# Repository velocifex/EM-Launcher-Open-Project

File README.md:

# Open-Source Electromagnetic Launcher (Coilgun) Development
This is a project to continually improve and implement open-source designs for coilguns, which are a type of electromagnetic (E.M.) launcher. This repository has files and information about the hardware and software for the designs under development.

# Help Wanted!
>This repo currently encapsulates a working but underperforming prototype. **It is meant as a starting point to improve upon.**
>
>It would be very helpful if individuals with electrical engineering skills could contribute to the project, especially to improve the circuit design (both schematics and layout).
>
>As stated below, **"this coilgun project aims to become the long-developed, widespread project that always could have been, but sadly never was."**

# Legality Notice
Physically producing some parts of this project may be legally prohibited in some jurisdictions. Please be aware of any laws that may apply to you before participating in this project in any way.

# Overview Explanation
Here is one very good and quick explanation of coilguns:
https://www.youtube.com/shorts/EF3v-DWCZcQ

In summary, a coilgun is fundamentally a type of electromagnetic motor, a linear switched reluctance motor to be exact. Like other electric motors it has:
- An armature to be moved. On rotating motors this is the rotor, and on a coilgun it is the projectile or launch vehicle.
	- For most coilguns including this one, the projectile is made partly or entirely of ferromagnetic material.
- Electromagnets to exert a force. On rotating motors this is the stator, while on a coilgun they are arranged along the launch track or "barrel".
	- For most coilguns including this one, these are solenoids. Usually the cross-sectional shape is circular, but this project has experimented with flat-plate rectangles as well.
	- There are usually sets of coils connected as a "phase" in rotating motors, while in coilguns there is usually one coil per "stage".
- Sensors to detect the position of the armature so the right coil(s) can be turned on or off.
- Control circuitry to switch power to specific coils on or off. This could be simply hooking up the coils' switches directly to the sensors in some ways, or using a microcontroller to have more complex switching behavior.
	- In this coilgun project, a microcontroller has been used so far, but a more simple logic circuit could be developed.

# Contents
This repo has files and instructions to do or make the following to construct the current (starting) version of the prototype:
- PCBs from online prototyping services for parts like the power switching circuits. These are in the "Hardware/Electrical" folder.
- Circuits on soldered or solderless prototyping boards for other parts that do not have or need PCBs. These are also in the "Hardware/Electrical" folder.
- 3D print the structural parts like the bobbins for the electromagnet coils. These are in the "Hardware/Mechanical" folder.
- Program microcontrollers to read sensors and switch the coils on or off. These are in the "Software" folder.
To reiterate: this prototype is just the most recent one in development, it has not yet fully achieved the project goal. The information provided in this repo is mainly to see how it was designed, so that it may be improved.

# Goals and Progress
The first milestone goal of this project is to make a coilgun which can launch something with **100m/s speed** and preferably as close to **100J kinetic energy** as possible.
Ideally it should be as energy-efficient as possible too, to make the design feasible to scale up or implement in any real-world use case.

Tests of this repo's developmental prototype as of November 14, 2026 have only achieved about 20m/s with a 44g (.044kg) projectile, giving about 8.8J of kinetic energy. This is about 9% efficient, which is above average for coilgun designs.

The project goal is proven to be feasible with existing commodity components! Several academic and hobbyist/amateur designs have already achieved such performance, but were never made open-source or otherwise did not see further development or community participation. **This coilgun project aims to become the long-developed, widespread project that always could have been, but sadly never was.**

# Possible Next Steps
- **Optimize coil geometry** i.e. wire diameter and number of turns, and consequently its electrical characteristics i.e. inductance and resistance, to create the most force! While also being decently efficient.
	- This is really the main problem to solve for a coilgun!
	- A technique for optimizing the coils has been developed, but it should be scrutinized by others. It's also very technical so it will not be repeated right here.
- Better projectile position sensors, preferably based on inductive sensing.
	- There could be a separate sensor coil in place of the existing photo-gate or contact sensors now, or sensing could be tried on the drive coils themselves.
- Change the control circuit to a simple logic-gate circuit that each stage has a copy of.
	- Would not directly improve efficiency but might make scaling up the number of stages easier.
- Capacitor energy recovery after coils shut off.
	- This would likely require high and low side switching of power to the coils which adds complexity to the power circuit design.
- Gate drive transformer for the power transistors instead of gate driver ICs.
	- This could help simplify the power switching circuit design, especially if it is going to be changed to high and low side switching.
- Set up a simulation to test lots of coil shapes more quickly than building them physically.
	- FreeCAD and ElmerFEM together would work great for this.
- Try different projectile shapes like the typical cylinder or maybe hollow ring/tube. The coils' cross-sectional shape would be different but the strategy to optimize them would be the same.
	- All existing switching and sensing components could be reused regardless of coil shape.

# Other Good Coilgun Projects
- Levi Janssen
	- Youtube channel: https://www.youtube.com/c/LeviJanssen
	- Series of videos about coilgun design:
		- https://www.youtube.com/watch?v=Xh28YdN8uP0&list=PLKl_Ihtuj1fpWz5WA09WJIgf677wJ2ihX (playlist)
		- https://www.youtube.com/watch?v=n-MfA9tIX5s and https://www.youtube.com/watch?v=OzI8P56p3pk (these last two videos in the series aren't in the above playlist)
- Electronoobs
	- Youtube channel: https://www.youtube.com/@ELECTRONOOBS/featured
	- Some videos on his coilgun projects:
		- https://www.youtube.com/watch?v=bGfrwBl-Q-A
		- https://www.youtube.com/watch?v=vtoWxGVx5kA
- OwenAir8242
	- Youtube channel: https://www.youtube.com/@owenair8242
	- This channel has some very good performing coilguns that achieve the 100m/s goal:
		- https://www.youtube.com/watch?v=5a4ZcsGYLRs
		- https://www.youtube.com/shorts/ZIMWo178rbU
		- https://www.youtube.com/shorts/G4_D2fhIGVg
- Tokamake
	- Youtube channel: https://www.youtube.com/@Tokamake
	- There are some excellently performing coilguns on this channel, including ones that much exceed the 100m/s speed goal! For example:
		- https://www.youtube.com/shorts/MI6NMF4MVIE
		- https://www.youtube.com/shorts/5vRxPeuDqeQ
		- https://www.youtube.com/shorts/phLoA5XnM9Y
- Owen Welsh
	- Youtube channel: https://www.youtube.com/@owensprojects
	- Some videos on his coilgun projects:
		- https://www.youtube.com/watch?v=BBhZLNdyRro
		- https://www.youtube.com/watch?v=rotrRg4ZUpk
		- https://www.youtube.com/watch?v=9OQUBITIkow

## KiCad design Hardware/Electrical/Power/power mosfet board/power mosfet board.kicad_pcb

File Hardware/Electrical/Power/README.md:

This is the circuit which turns power to one coil on or off. Below are some pictures and descriptions of the parts on the PCB.
The most important part is the high-power MOSFET which is a type of transistor switch. This particular design uses Goford brand MOSFET, product code GT020N10TL, which is rated to 100V drain-to-source and 300A continuous current, although it can briefly handle higher currents if done infrequently.
The next most important part is the MOSFET gate driver IC which helps quickly and safely make the MOSFET conductive or not, corresponding to the coil being powered "on" or "off" respectively. It also provides galvanic isolation between the low-voltage control circuitry and higher-voltage main power rails for safety. Accordingly, it has its own +15V isolated power supply located on another board (not shown below) and plugged into one of the connectors. Each board has two power supply input connectors so they can be daisy-chained together and use less wire.
Another important part is the flyback diode (also called crowbar diode) which lets the coil current continue flowing briefly after it is shut off (disconnected from main power) and dissipate its energy through its own wire resistance. Without this component, there would be a huge inductive voltage spike across the MOSFET when it tries to stop conducting, which could easily cause breakdown and destroy it.
This version of the circuit uses only low-side switching to reduce the cost and complexity of having to switch an N-channel MOSFET at the high side or having to find a corresponding P-channel MOSFET with similar power ratings.

Front view:

Back view:

The board could technically be facing in any direction as long as the terminal connections to the coil and power are correct. The "front" and "back" are just nominal designations.

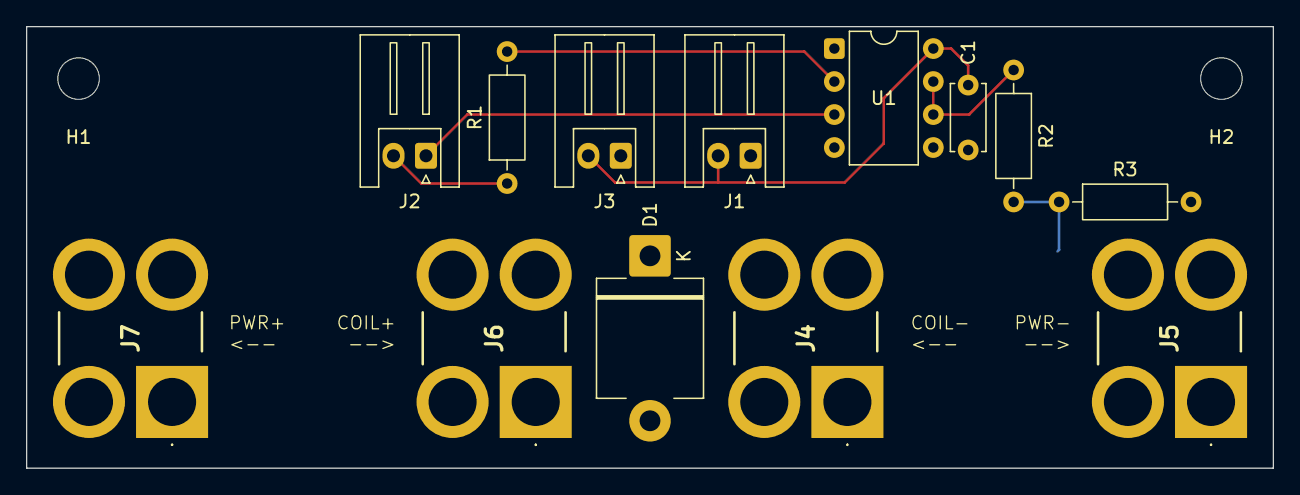
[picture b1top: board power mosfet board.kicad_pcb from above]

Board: 2 copper layers, 96.0 x 34.0 mm, 16 parts (1 on the bottom side), 9 nets.

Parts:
C1: 0.1uF; C_Disc_D5.0mm_W2.5mm_P5.00mm
D1: flyback; D_5KPW_P12.70mm_Horizontal
H1, H2: MountingHole; MountingHole_3.2mm_M3_DIN965
J1, J2, J3: Conn_01x02; JST_XH_S2B-XH-A_1x02_P2.50mm_Horizontal
J4, J5, J6, J7: Screw_Terminal_01x01; AMT0440008TH0000G
Q1: POWER MOSFET; Infineon_PG-HSOF-8-1
R1: 270Ohm; R_Axial_DIN0207_L6.3mm_D2.5mm_P10.16mm_Horizontal
R2: 5Ohm; R_Axial_DIN0207_L6.3mm_D2.5mm_P10.16mm_Horizontal
R3: 10kOhm; R_Axial_DIN0207_L6.3mm_D2.5mm_P10.16mm_Horizontal
U1: HCPL-3120; DIP-8_W7.62mm

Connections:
+15V: C1.1, J1.2, J3.2, U1.8 (VCC)
/drain: D1.2 (A), J4.1, J4.2, J4.3, J4.4, Q1.3 (D)
/gate: Q1.1 (G), R2.2, R3.1
/high side: D1.1 (K), J6.1, J6.2, J6.3, J6.4, J7.1, J7.2, J7.3, J7.4
GND: C1.2, J1.1, J3.1, J5.1, J5.2, J5.3, J5.4, Q1.2 (S), R3.2, U1.5 (VEE)
unnamed: J2.1, U1.3 (C)
unnamed: J2.2, R1.1
unnamed: R2.1, U1.6 (VO), U1.7 (VO)
unnamed: R1.2, U1.2 (A)
